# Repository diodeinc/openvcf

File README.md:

# OpenVCF

Open-source, customizable PCB printed business cards with writable NFC tag, powered by @atopile. The name is a reference to the [VCF](https://en.wikipedia.org/wiki/VCard)
format.

https://github.com/user-attachments/assets/a1362707-7bfc-4f3d-abbb-3289b361ead8

## Schematics

Schematics are really straighforward, with just 4 components

- Capacitor to smooth the NFC power generation.
- Resistor to current limit the LED.
- A Yellow LED
- [NFC NTAG: NT3H1101W0FHKH](card/elec/src/nfc/NT3H1101W0FHKH.ato)

The NT3H1101W0FHKH is really cool, a writable NFC tag that just needs an antenna.
It will generate enough power from the NFC field to light up a LED.

## Ordering 

DM on [twitter](https://x.com/davideasnaghi) if you want us to send you one of 
these. You can even customize it with your logo!

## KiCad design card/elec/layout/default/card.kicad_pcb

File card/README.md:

# OpenVCF card

Atopile package for a business card based on NFC.

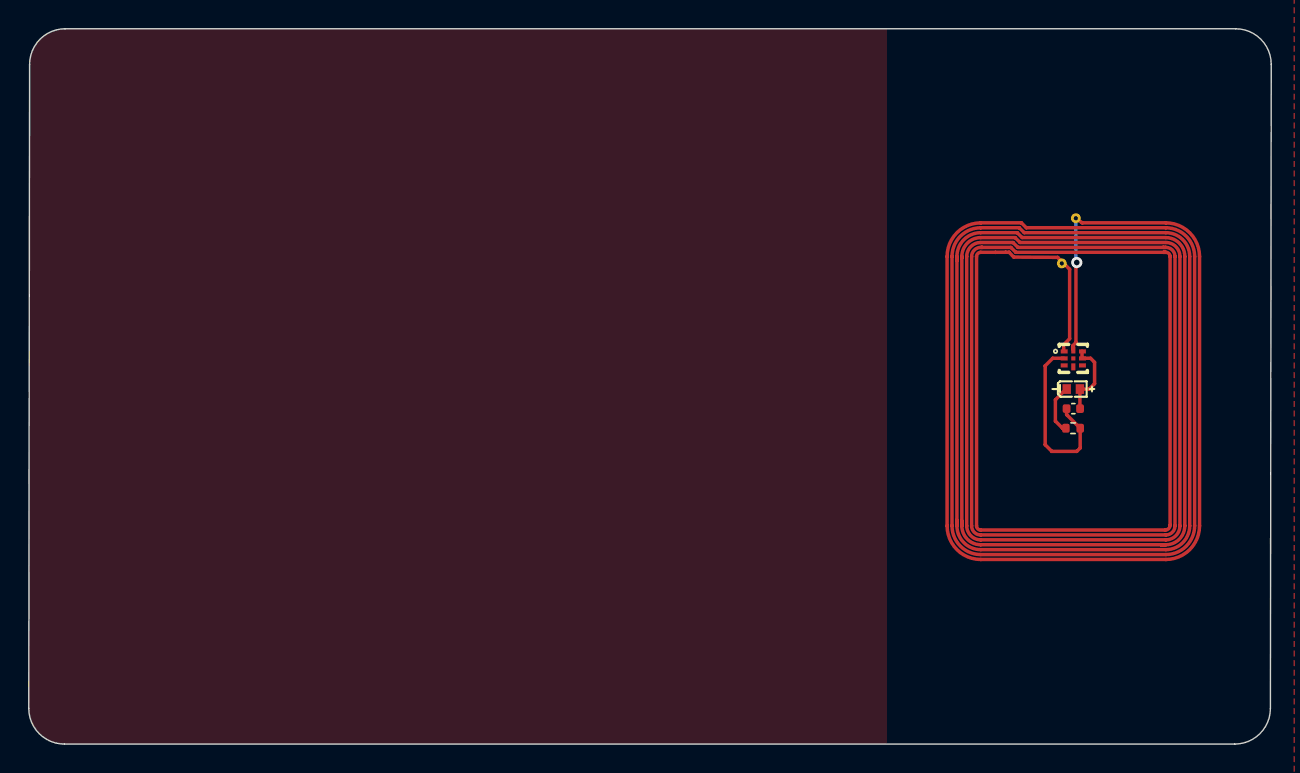
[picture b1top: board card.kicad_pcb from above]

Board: 2 copper layers, 88.6 x 51.0 mm, 5 parts (0 on the bottom side), 5 nets.

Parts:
C1: 16V 220nF X7R ±10% 0402 Multilayer Ceramic Capaci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; C0402
LED1: LED-SMD_L1.0-W0.5-RD
R1: 62.5mW Thick Film Resistors 50V ±100ppm/℃ ±5% 50Ω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; R0402
U1: HM-NFC-Class6-Antenna
U2: XQFN-8_L1.6-W1.6-P0.50-BR

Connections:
cathode: LED1.1, R1.1
gnd: C1.2, R1.2, U2.2
la: U1.1, U2.1
lb: U1.2, U2.8
vcc: C1.1, LED1.2, U2.6, U2.7

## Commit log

2024-05-01 [INIT] readme
2024-05-01 [README] atopile
2024-05-01 [ATO] init project
2024-05-01 [ATO] add NFC component
2024-05-01 [ATO] install from JLC
2024-05-02 [NFC] antenna
2024-05-02 [NFC] add LED
2024-05-04 [NFC] import LED SMD
2024-05-04 [MECH] add logo
2024-05-04 [MECH] simpler logo
2024-05-04 [KICAD] add logo to front
2024-05-04 [KICAD] openvcf
2024-05-04 [KICAD] complete routing
2024-05-07 [KICAD] remove copper from under the antenna
2024-05-24 [OPENVCF] remove copper from antenna
2024-07-04 [LOGO] use dxf
2024-08-01 [README] image
2024-08-01 [README] video
2024-08-01 [README] shorter
2024-08-01 [README] add atopile
2024-08-02 [MEDIA] remove
2024-08-02 [CI] fix
2024-08-02 [ATOPILE] logo
2024-08-09 [DIODE] name
2024-08-15 [OWAY] PCB
2024-10-29 [PCB] amend resisor value
2024-10-29 [PCB] fix capacitance
2024-10-29 fix capacitance
